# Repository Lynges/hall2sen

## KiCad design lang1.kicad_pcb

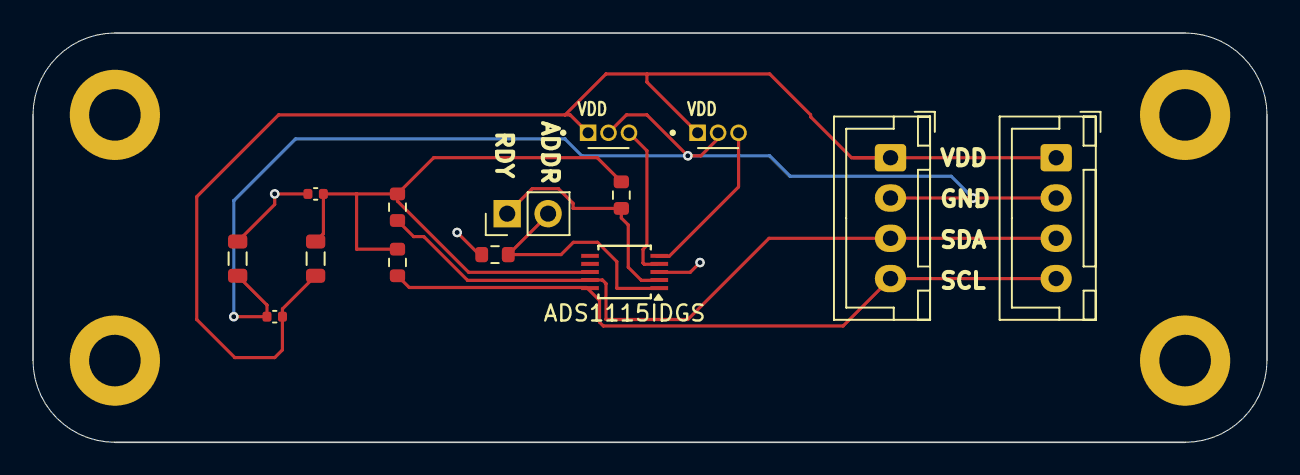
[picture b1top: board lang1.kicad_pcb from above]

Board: 2 copper layers, 76.6 x 25.4 mm, 18 parts (0 on the bottom side), 9 nets.

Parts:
ADS1115IDGS: ADS1115IDGS; TSSOP-10_3x3mm_P0.5mm
C1, C2: 1µF; C_0402_1005Metric
FB1, FB2: GZ2012D152TF; L_0805_2012Metric
H1, H2, H3, H4: MountingHole; MountingHole_3.2mm_M3_DIN965_Pad
J1, J2: Conn_01x04; JST_XH_B4B-XH-A_1x04_P2.50mm_Vertical
J3: Conn_01x02_Pin; PinHeader_1x02_P2.54mm_Vertical
R1, R2, R3, R4: 10K; R_0603_1608Metric
VDD: SS495A; XDCR_SS495A
VDD#2: SS495A; XDCR_SS495A

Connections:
/GND2: C1.1, FB1.2, J1.2, J2.2, VDD.2 (GND), VDD#2.2 (GND)
GND: ADS1115IDGS.3 (GND), C2.1, FB1.1, R1.2
unnamed: ADS1115IDGS.9 (SDA), J1.3, J2.3, R4.2
unnamed: ADS1115IDGS.10 (SCL), J1.4, J2.4, R3.2
unnamed: ADS1115IDGS.2 (ALERT/RDY), J3.1, R2.2
unnamed: ADS1115IDGS.1 (ADDR), J3.2, R1.1
unnamed: ADS1115IDGS.4 (AIN0), VDD#2.3 (OUT)
unnamed: ADS1115IDGS.5 (AIN1), VDD.3 (OUT)
VDD: ADS1115IDGS.8 (VDD), C1.2, C2.2, FB2.1, FB2.2, J1.1, J2.1, R2.1, R3.1, R4.1, VDD.1 (VCC), VDD#2.1 (VCC)

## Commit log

2024-03-17 First
2024-03-19 senger
2024-03-19 taket nit
